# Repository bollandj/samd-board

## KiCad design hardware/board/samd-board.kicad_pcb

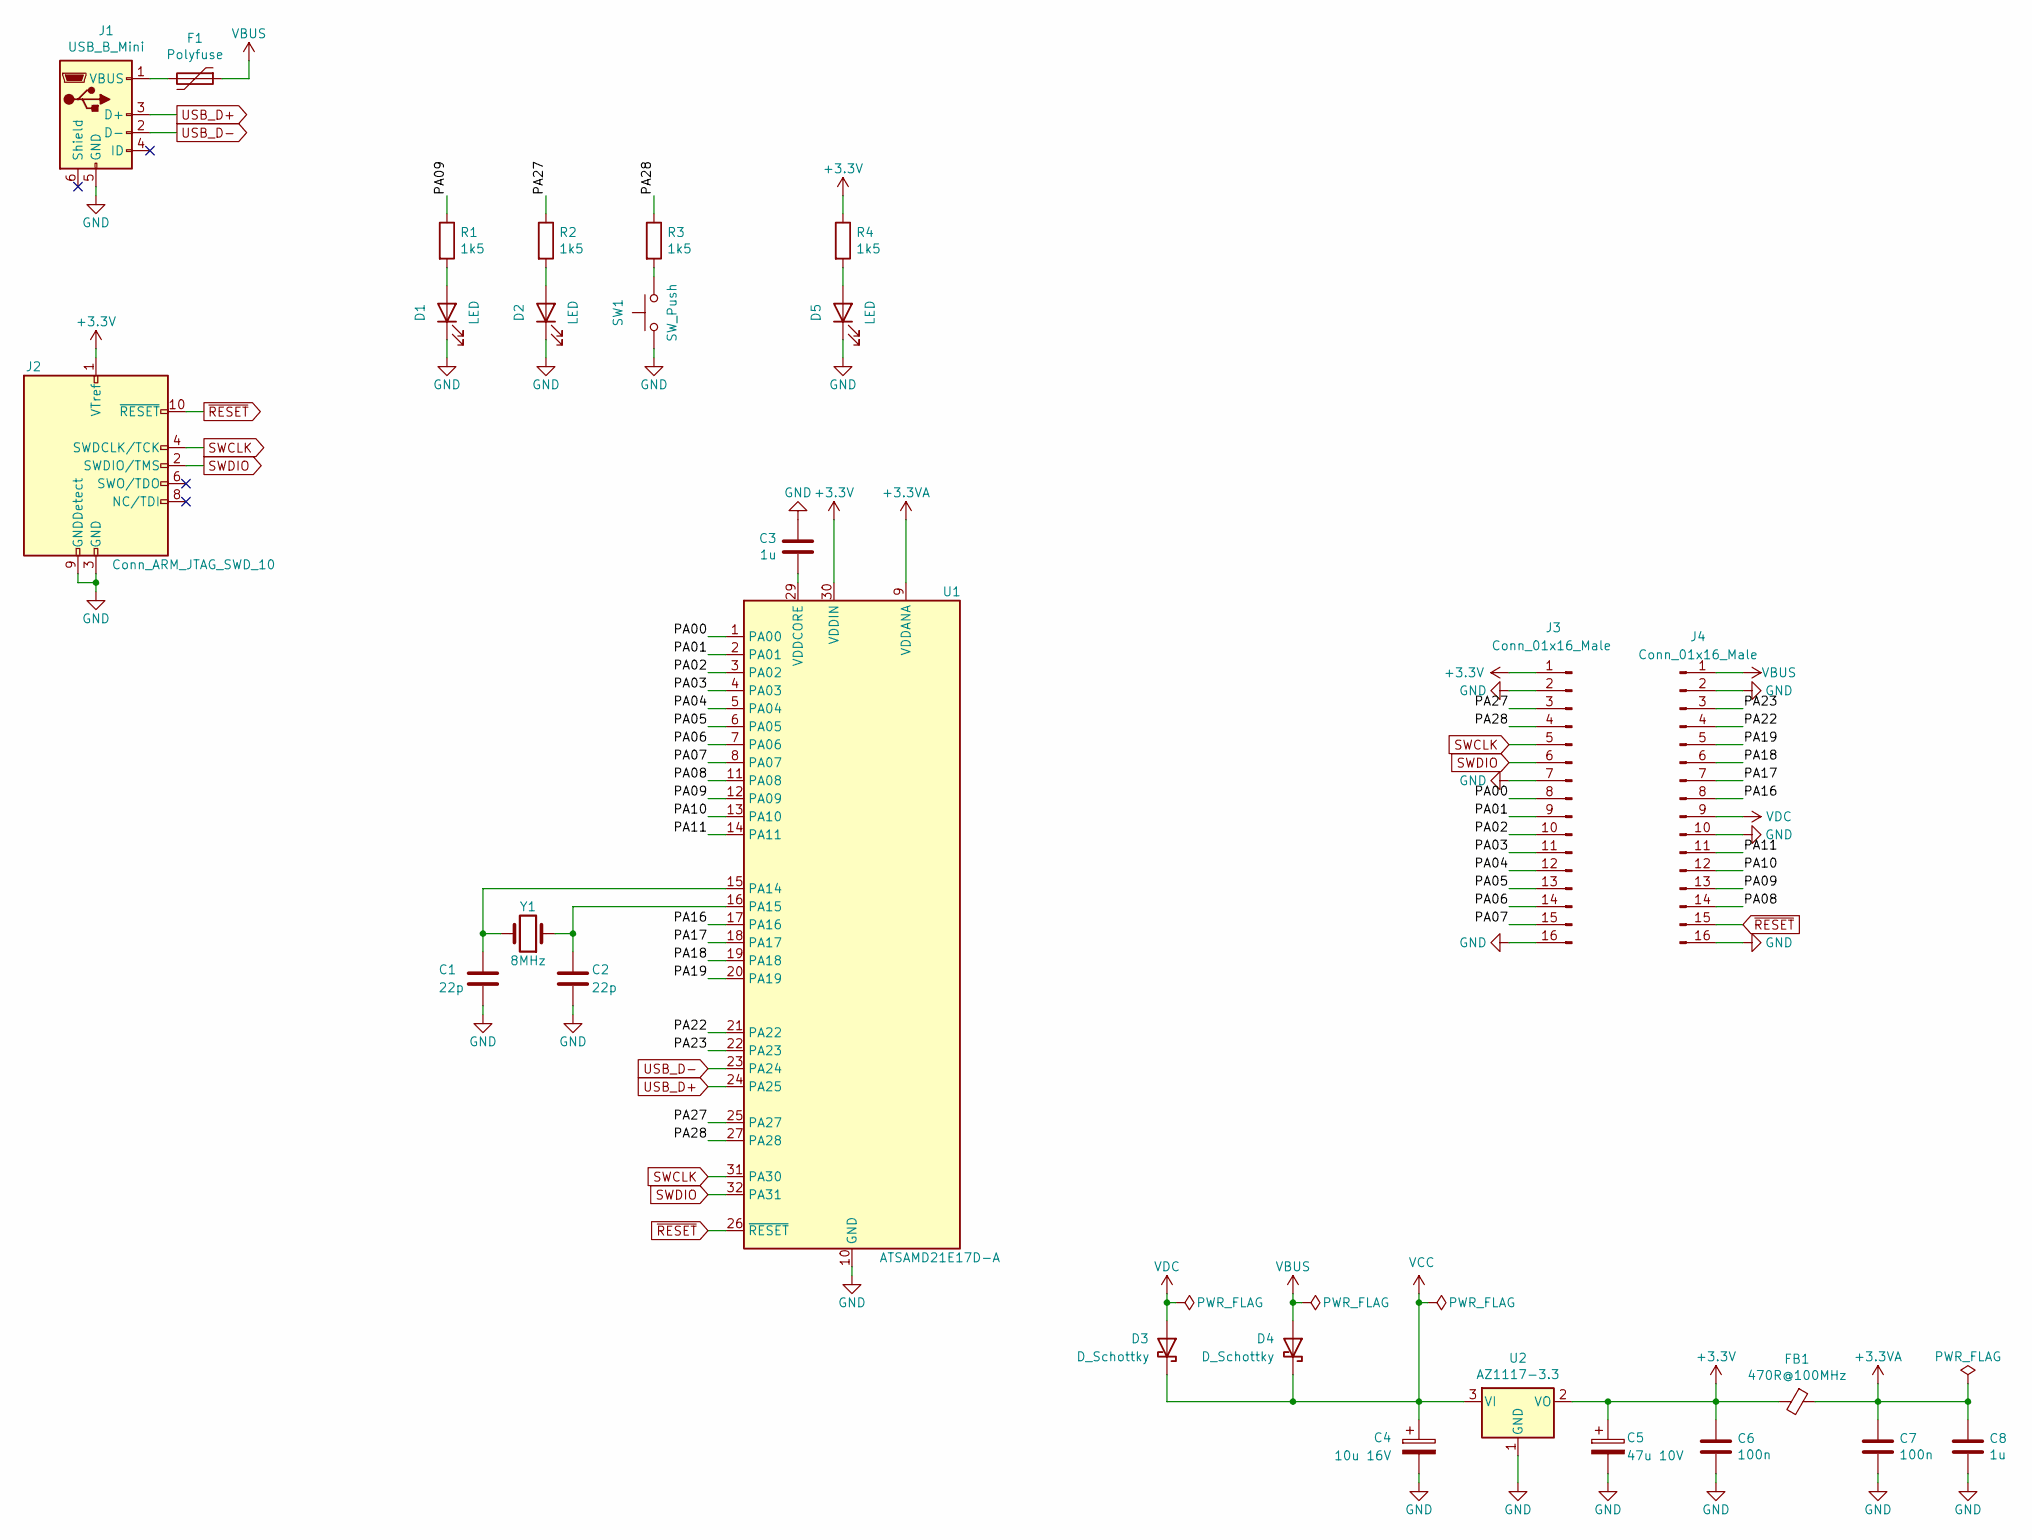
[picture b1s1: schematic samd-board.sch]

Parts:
C1, C2: 22p; C_0603_1608Metric_Pad1.08x0.95mm_HandSolder
C3, C8: 1u; C_0603_1608Metric_Pad1.08x0.95mm_HandSolder
C4: 10u 16V; CP_EIA-3216-18_Kemet-A_Pad1.58x1.35mm_HandSolder
C5: 47u 10V; CP_EIA-3528-21_Kemet-B_Pad1.50x2.35mm_HandSolder
C6, C7: 100n; C_0603_1608Metric_Pad1.08x0.95mm_HandSolder
D1, D2, D5: LED; LED_0603_1608Metric_Pad1.05x0.95mm_HandSolder
D3, D4: D_Schottky; D_SOD-123
F1: Polyfuse; R_1206_3216Metric_Pad1.30x1.75mm_HandSolder
FB1: 470R@100MHz; L_0603_1608Metric_Pad1.05x0.95mm_HandSolder
J1: USB_B_Mini; USB_Mini-B_Lumberg_2486_01_Horizontal
J2: Conn_ARM_JTAG_SWD_10; PinHeader_2x05_P1.27mm_Vertical
J3, J4: Conn_01x16_Male; PinHeader_1x16_P2.54mm_Vertical
R1, R2, R3, R4: 1k5; R_0603_1608Metric_Pad0.98x0.95mm_HandSolder
SW1: SW_Push; SW_SPST_CK_RS282G05A3
U1: ATSAMD21E17D-A; TQFP-32_7x7mm_P0.8mm
U2: AZ1117-3.3; SOT-223-3_TabPin2
Y1: 8MHz; Crystal_SMD_Abracon_ABM3-2Pin_5.0x3.2mm

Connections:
+3.3VA: C7.1, C8.1, FB1.1, U1.9 (VDDANA)
+3V3: C5.1, C6.1, FB1.2, J2.1 (VTref), J3.1, R4.1, U1.30 (VDDIN), U2.2 (VO)
/PA00: J3.8, U1.1 (PA00)
/PA01: J3.9, U1.2 (PA01)
/PA02: J3.10, U1.3 (PA02)
/PA03: J3.11, U1.4 (PA03)
/PA04: J3.12, U1.5 (PA04)
/PA05: J3.13, U1.6 (PA05)
/PA06: J3.14, U1.7 (PA06)
/PA07: J3.15, U1.8 (PA07)
/PA08: J4.14, U1.11 (PA08)
/PA09: J4.13, R1.1, U1.12 (PA09)
/PA10: J4.12, U1.13 (PA10)
/PA11: J4.11, U1.14 (PA11)
/PA16: J4.8, U1.17 (PA16)
/PA17: J4.7, U1.18 (PA17)
/PA18: J4.6, U1.19 (PA18)
/PA19: J4.5, U1.20 (PA19)
/PA22: J4.4, U1.21 (PA22)
/PA23: J4.3, U1.22 (PA23)
/PA27: J3.3, R2.1, U1.25 (PA27)
/PA28: J3.4, R3.1, U1.27 (PA28)
GND: C1.2, C2.2, C3.2, C4.2, C5.2, C6.2, C7.2, C8.2, D1.1 (K), D2.1 (K), D5.1 (K), J1.5 (GND), J2.3 (GND), J2.5 (GND), J2.9 (GNDDetect), J3.2, J3.7, J3.16, J4.2, J4.10, J4.16, SW1.1, U1.10 (GND), U1.28 (GND), U2.1 (GND); also elsewhere on the board
unnamed: C1.1, U1.15 (PA14), Y1.2
unnamed: C2.1, U1.16 (PA15), Y1.1
unnamed: C3.1, U1.29 (VDDCORE)
unnamed: D1.2 (A), R1.2
unnamed: D2.2 (A), R2.2
unnamed: D5.2 (A), R4.2
unnamed: F1.2, J1.1 (VBUS)
unnamed 35: R3.2, SW1.2; also elsewhere on the board
SWCLK: J2.4 (SWDCLK/TCK), J3.5, U1.31 (PA30)
SWDIO: J2.2 (SWDIO/TMS), J3.6, U1.32 (PA31)
USB_D+: J1.3 (D+), U1.24 (PA25)
USB_D-: J1.2 (D-), U1.23 (PA24)
VBUS: D4.2 (A), F1.1, J4.1
VCC: C4.1, D3.1 (K), D4.1 (K), U2.3 (VI)
VDC: D3.2 (A), J4.9
~RESET: J2.10 (~RESET~), J4.15, U1.26 (~RESET)

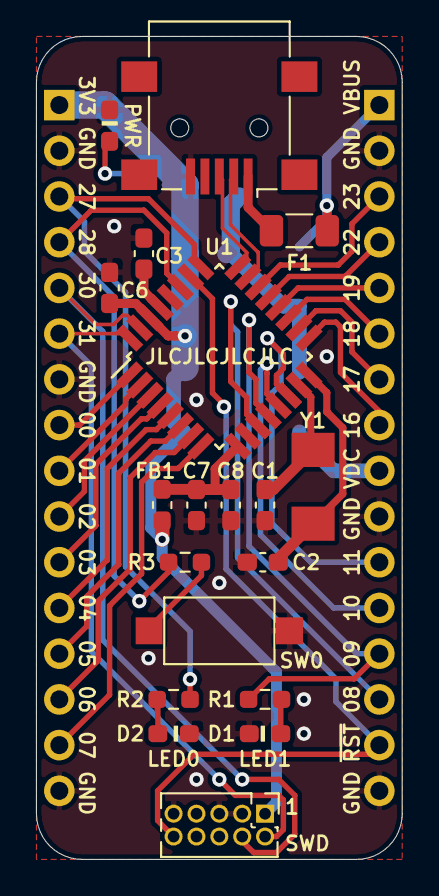
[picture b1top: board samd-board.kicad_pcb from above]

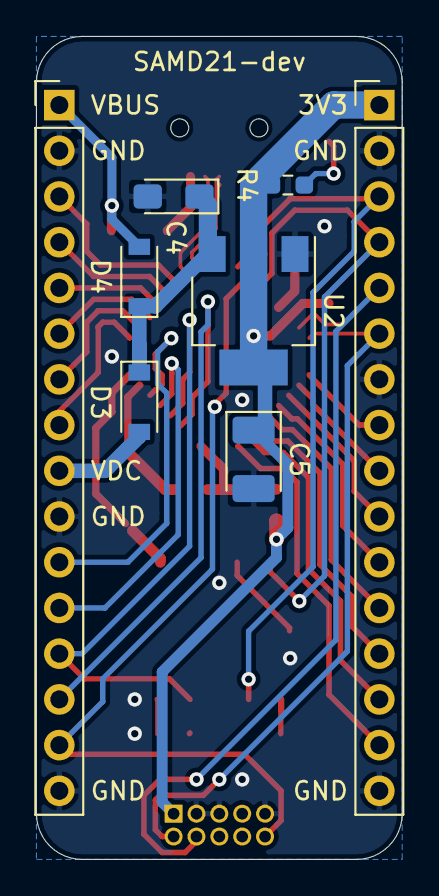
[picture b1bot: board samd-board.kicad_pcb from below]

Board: 2 copper layers, 20.3 x 45.7 mm, 27 parts (8 on the bottom side), 39 nets.

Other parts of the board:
SW0: SW_Push; SW_SPST_CK_RS282G05A3

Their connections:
GND: SW0.1; also elsewhere on the board
unnamed 35: SW0.2; also elsewhere on the board

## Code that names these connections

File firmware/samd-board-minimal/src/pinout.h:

#ifndef PINOUT_H
#define PINOUT_H

/* 
    GPIO 
*/

#define PORTA 0 // PORTA group number

#define GPIO_PORT PORTA

#define LED0_PORT PORT_PA09
#define LED0_PIN  PIN_PA09

#define LED1_PORT PORT_PA27
#define LED1_PIN  PIN_PA27

#define SW0_PORT PORT_PA28
#define SW0_PIN  PIN_PA28

/* 
    USART
*/

#define USART_TX_PORT     PORT_PA16
#define USART_TX_PIN      PIN_PA16
#define USART_TX_PMUX_Val PORT_PMUX_PMUXE_D_Val
#define USART_TXPO_Val    1 // PAD[2]      

#define USART_RX_PORT     PORT_PA17
#define USART_RX_PIN      PIN_PA17
#define USART_RX_PMUX_Val PORT_PMUX_PMUXE_D_Val
#define USART_RXPO_Val    3 // PAD[3]

#endif // PINOUT_H

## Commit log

2021-07-03 complete basic routing
2021-07-04 increase pin count from 28 to 32, complete routing
2021-07-04 complete component silkscreen placement
2021-07-05 add power LED, pin silkscreen markers
2021-07-05 complete board
2021-07-19 added minimal firmware example
